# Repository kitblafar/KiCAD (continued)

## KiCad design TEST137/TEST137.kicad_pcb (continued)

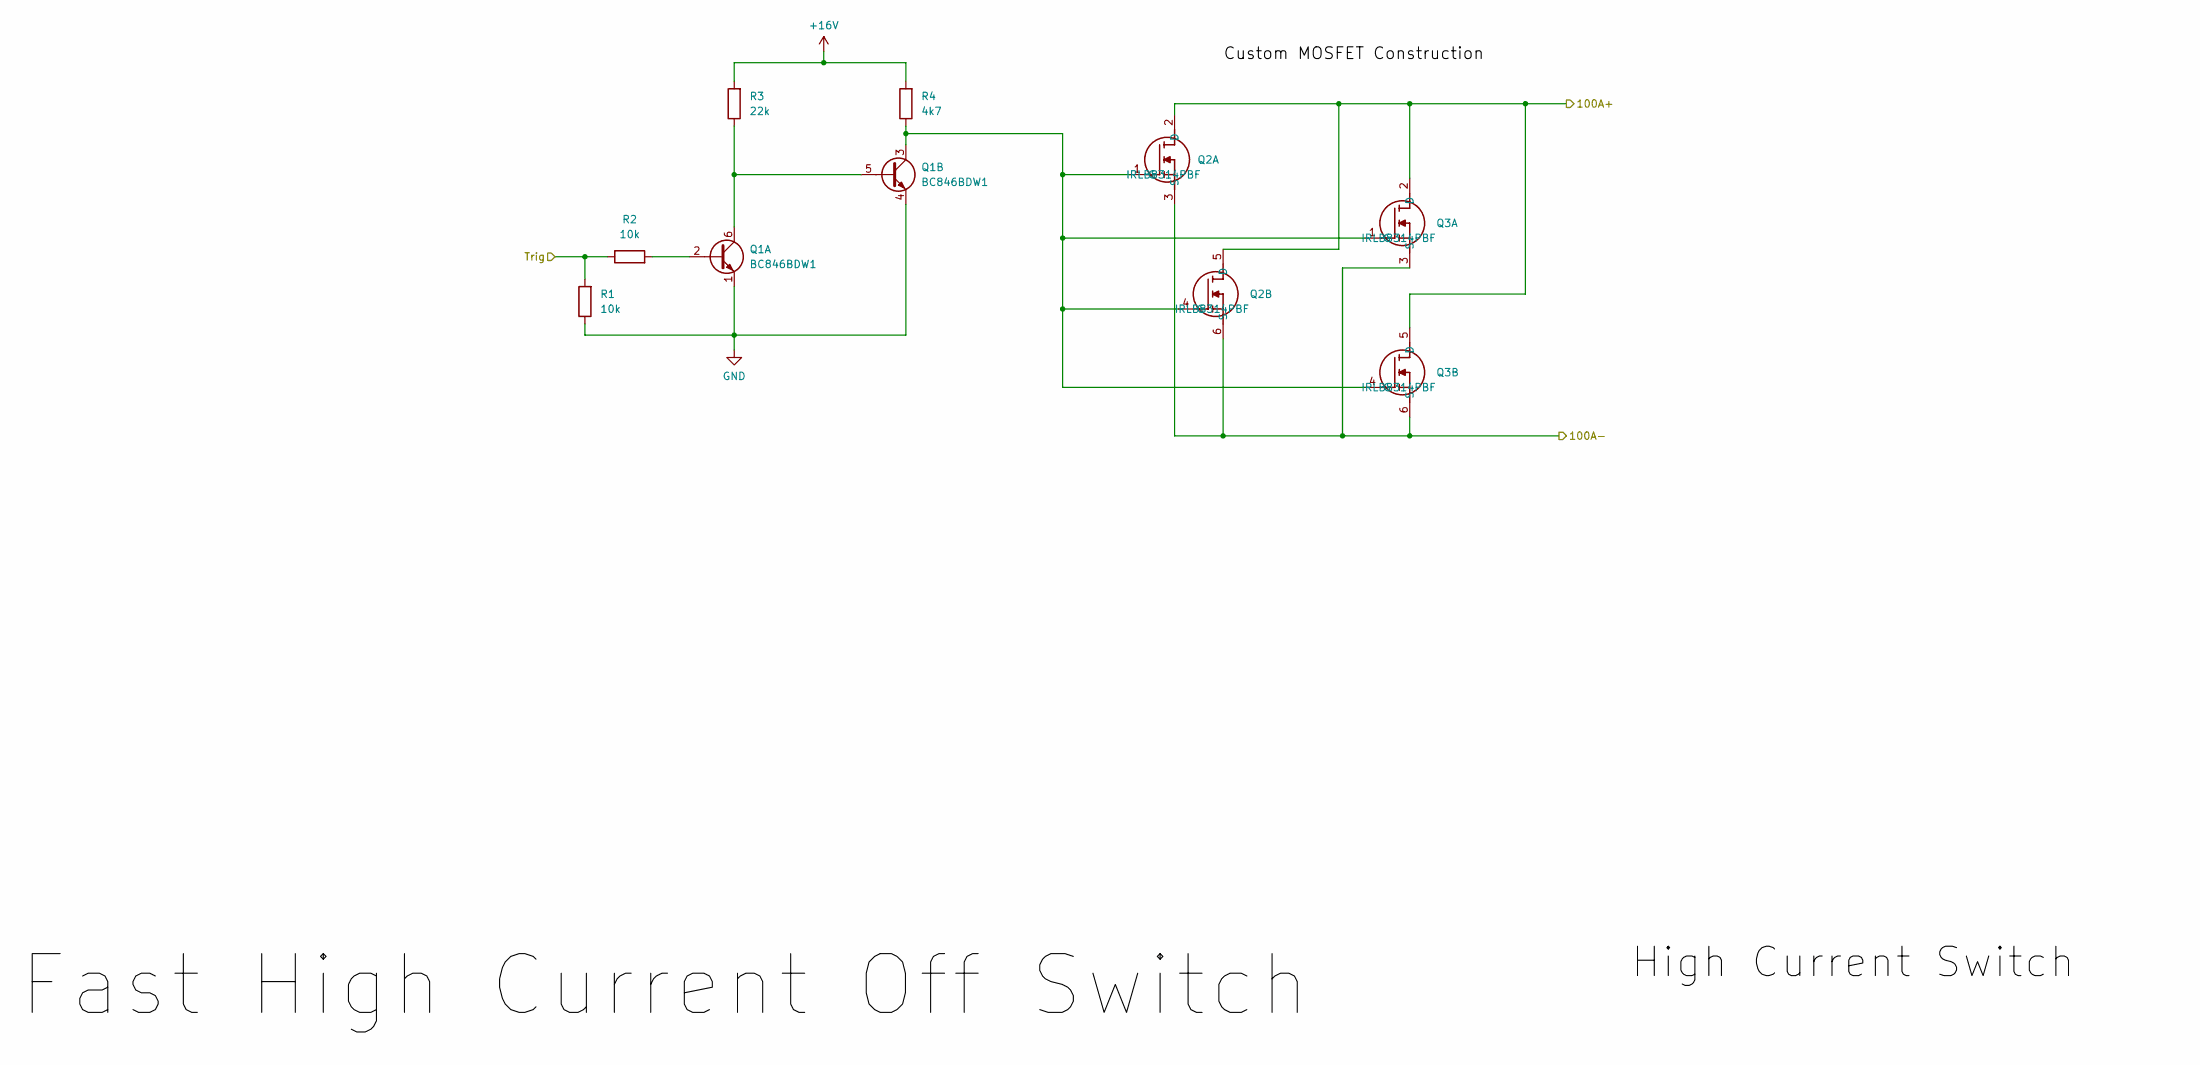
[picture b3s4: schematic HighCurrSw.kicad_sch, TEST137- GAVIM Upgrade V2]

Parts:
Q1: BC846BDW1; SOT-363_SC-70-6
Q2, Q3: IRLB8314PBF; MOSFETConstruct
R1, R2: 10k; R_0603_1608Metric_Pad0.98x0.95mm_HandSolder; Mouser Part Number LM321
R3: 22k; R_0603_1608Metric_Pad0.98x0.95mm_HandSolder
R4: 4k7; R_0603_1608Metric_Pad0.98x0.95mm_HandSolder

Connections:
+16V: R3.2, R4.2; also elsewhere on the board
/High Current Switch/100A+: Q2.2 (D), Q2.5 (D), Q3.2 (D), Q3.5 (D); also elsewhere on the board
/High Current Switch/100A-: Q2.3 (S), Q2.6 (S), Q3.3 (S), Q3.6 (S); also elsewhere on the board
/High Current Switch/Trig: R1.2, R2.1; also elsewhere on the board
GND: Q1.1 (E1), Q1.4 (E2), R1.1; also elsewhere on the board
unnamed: Q1.2 (B1), R2.2
unnamed: Q1.5 (B2), Q1.6 (C1), R3.1
unnamed: Q1.3 (C2), Q2.1 (G), Q2.4 (G), Q3.1 (G), Q3.4 (G), R4.1

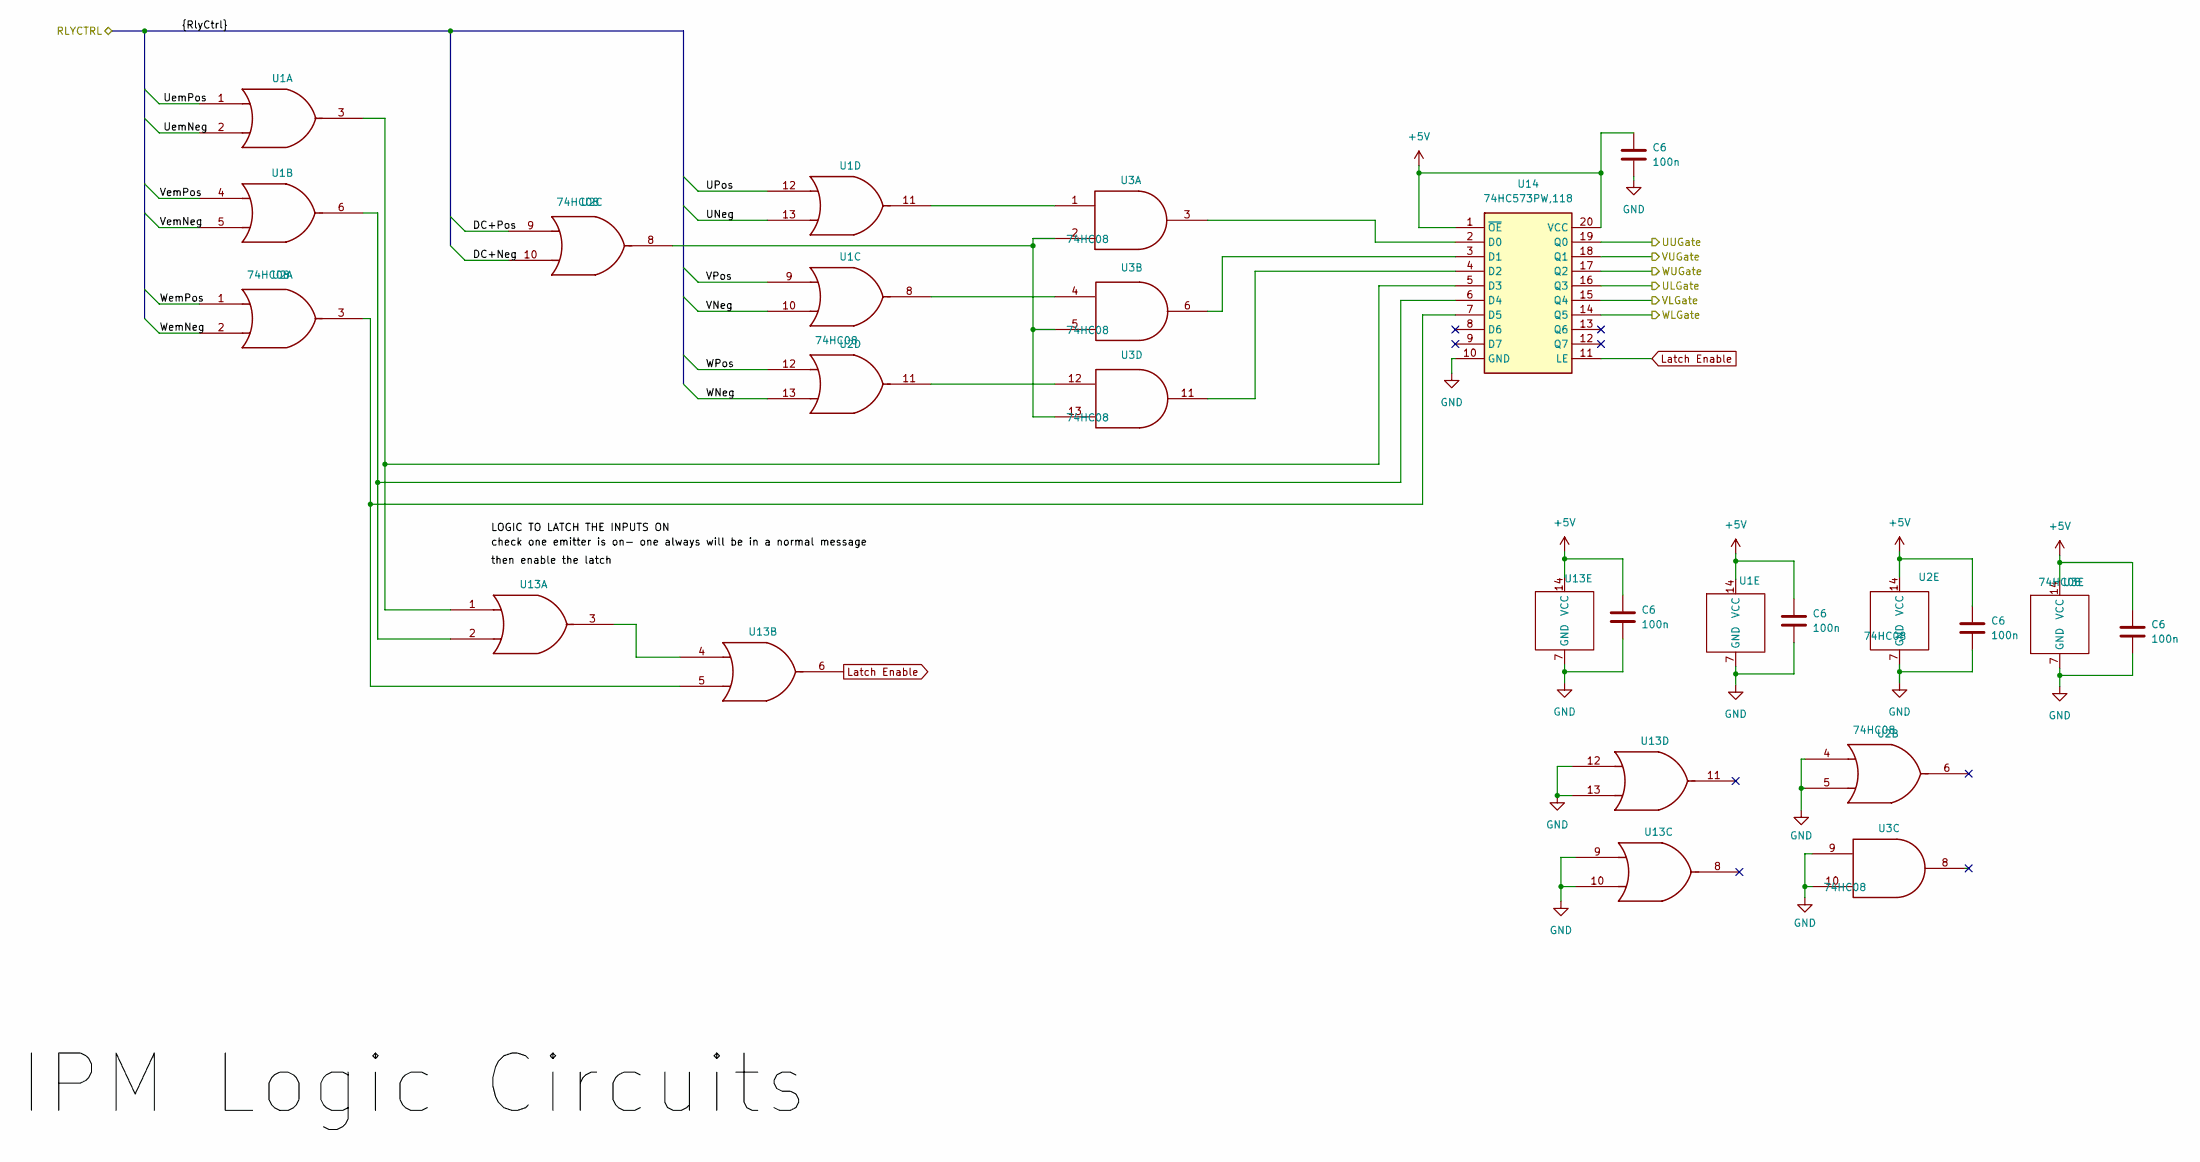
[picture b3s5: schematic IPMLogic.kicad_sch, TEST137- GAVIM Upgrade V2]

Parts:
C6: 100n; C_0603_1608Metric_Pad1.08x0.95mm_HandSolder
U1, U13: 74HC32; SO-14_3.9x8.65mm_P1.27mm
U2, U3: 74HC08; SO-14_3.9x8.65mm_P1.27mm
U14: 74HC573PW,118; SOP65P640X110-20N; Mouser Part Number 771-74HC573PW-T

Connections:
/DC+Neg: U2.10; also elsewhere on the board
/DC+Pos: U2.9; also elsewhere on the board
/IPM Logic/ULGate: U14.16 (Q3); also elsewhere on the board
/IPM Logic/UUGate: U14.19 (Q0); also elsewhere on the board
/IPM Logic/VLGate: U14.15 (Q4); also elsewhere on the board
/IPM Logic/VUGate: U14.18 (Q1); also elsewhere on the board
/IPM Logic/WLGate: U14.14 (Q5); also elsewhere on the board
/IPM Logic/WUGate: U14.17 (Q2); also elsewhere on the board
/UNeg: U1.13; also elsewhere on the board
/UPos: U1.12; also elsewhere on the board
/UemNeg: U1.2; also elsewhere on the board
/UemPos: U1.1; also elsewhere on the board
/VNeg: U1.10; also elsewhere on the board
/VPos: U1.9; also elsewhere on the board
/VemNeg: U1.5; also elsewhere on the board
/VemPos: U1.4; also elsewhere on the board
/WNeg: U2.13; also elsewhere on the board
/WPos: U2.12; also elsewhere on the board
/WemNeg: U2.2; also elsewhere on the board
/WemPos: U2.1; also elsewhere on the board
GND: C6.2, U1.7 (GND), U2.4, U2.5, U2.7 (GND), U3.7 (GND), U3.9, U3.10, U13.7 (GND), U13.9, U13.10, U13.12, U13.13, U14.10 (GND); also elsewhere on the board
Latch Enable: U13.6, U14.11 (LE)
unnamed: U1.8, U3.4
unnamed: U1.11, U3.1
unnamed: U2.8, U3.2, U3.5, U3.13
unnamed: U2.11, U3.12
unnamed: U13.3, U13.4
unnamed: U3.3, U14.2 (D0)
unnamed: U3.6, U14.3 (D1)
unnamed: U3.11, U14.4 (D2)
unnamed: U1.3, U13.1, U14.5 (D3)
unnamed: U1.6, U13.2, U14.6 (D4)
unnamed: U2.3, U13.5, U14.7 (D5)

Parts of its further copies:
C9, C12, C15, C18, C21, C24, C27, C28, C29, C30, C31: 100n; C_0603_1608Metric_Pad1.08x0.95mm_HandSolder

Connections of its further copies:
GND: C9.2, C12.2, C15.2, C18.2, C21.2, C24.2, C27.2, C28.2, C29.2, C30.2, C31.2; also elsewhere on the board

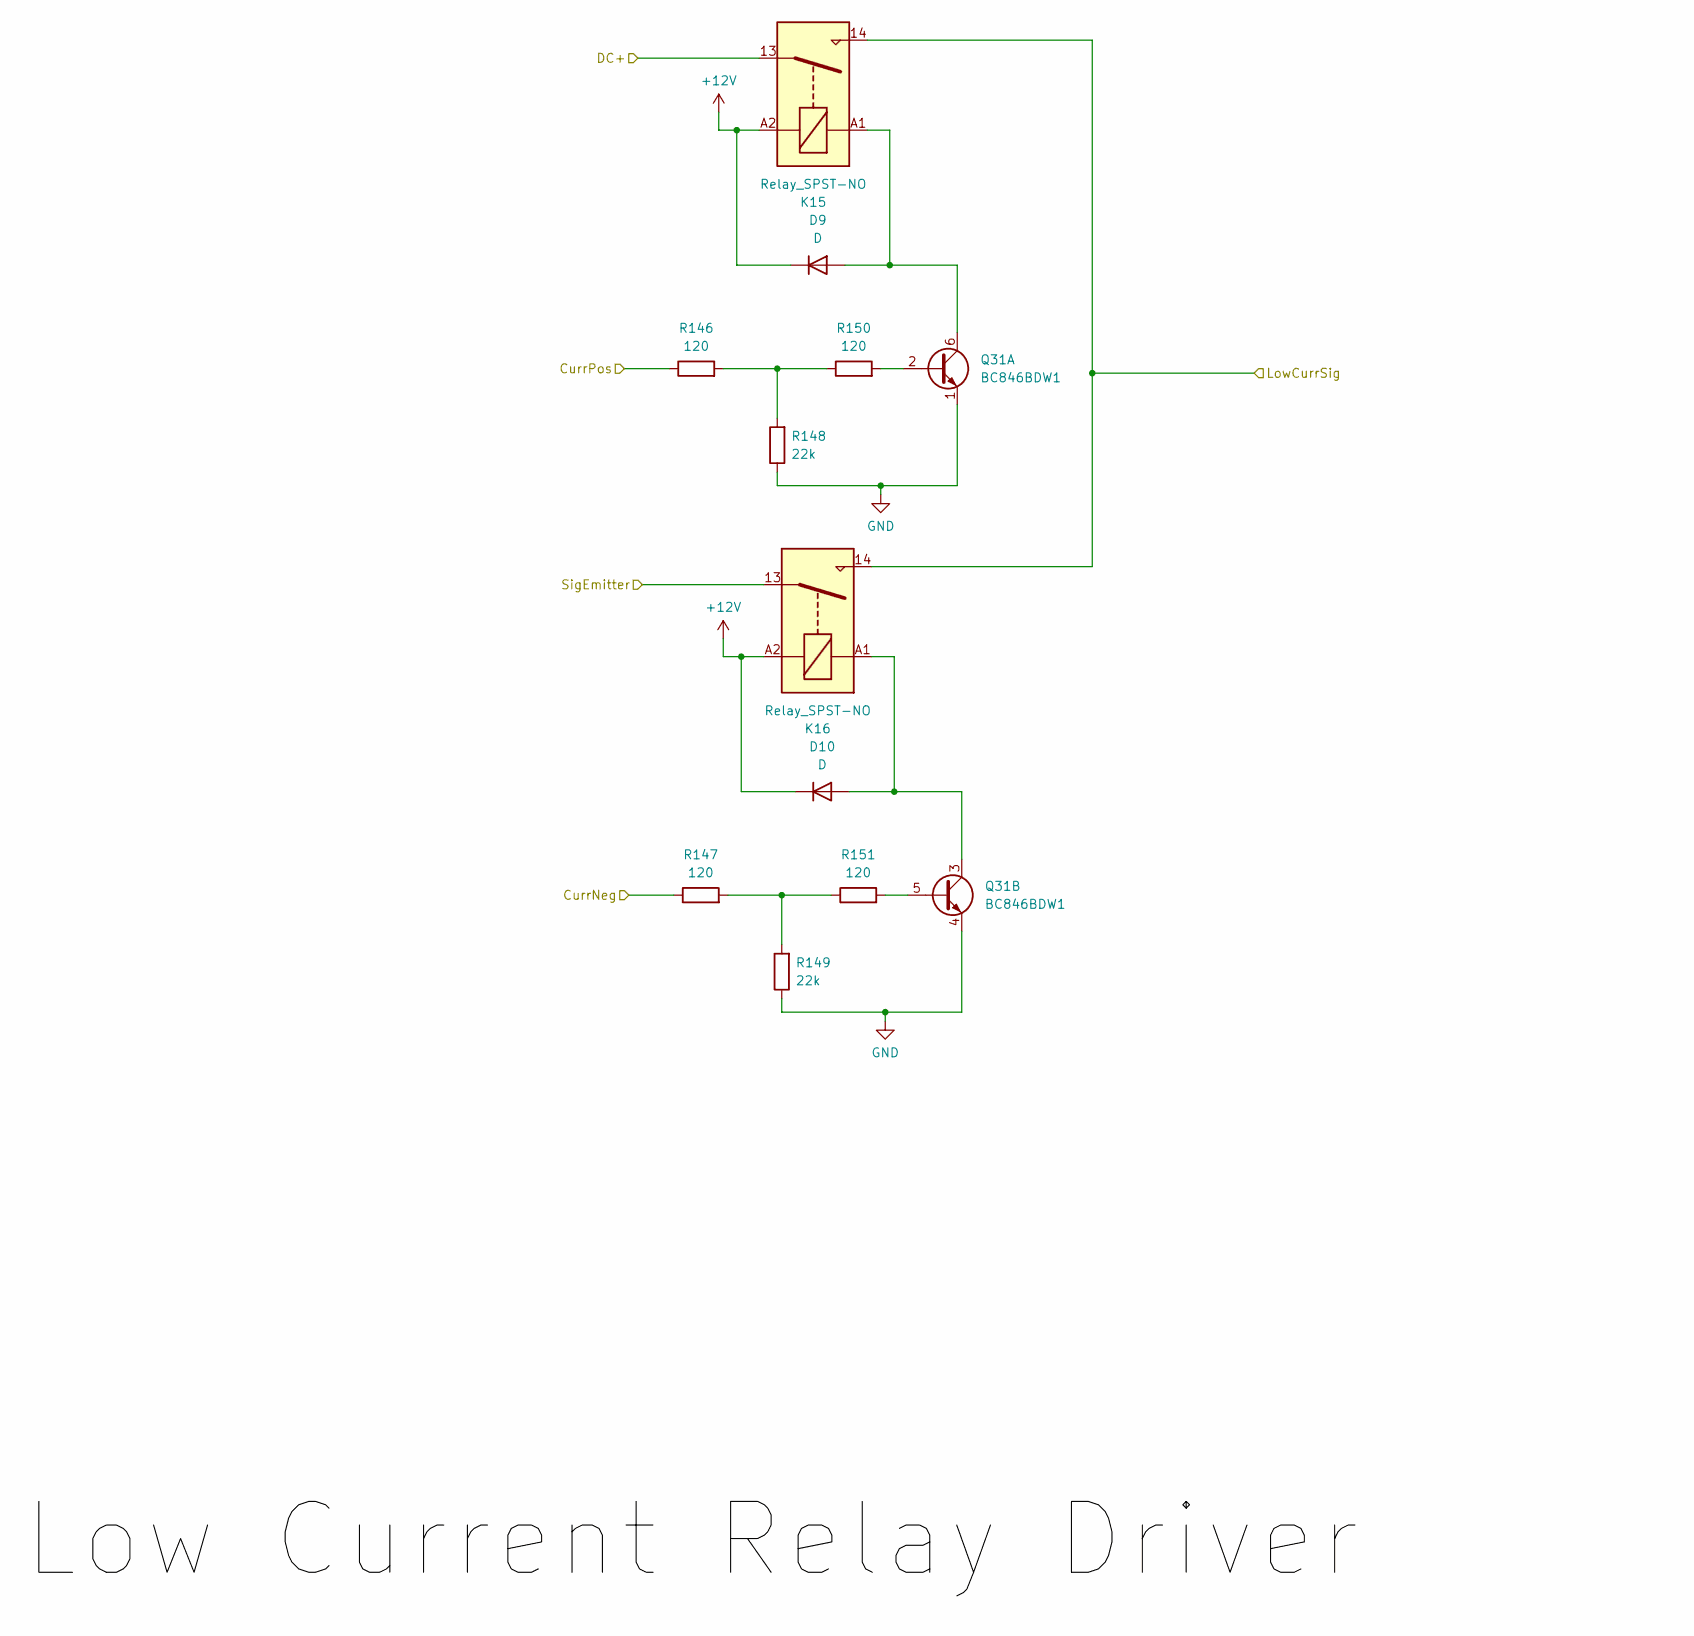
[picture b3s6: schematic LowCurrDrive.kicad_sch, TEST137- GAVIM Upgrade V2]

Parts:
D9, D10: D; D_DO-41_SOD81_P12.70mm_Horizontal
K15, K16: Relay_SPST-NO; HF32FAG012HSL1
Q31: BC846BDW1; SOT-363_SC-70-6
R146, R147, R150, R151: 120; R_0603_1608Metric_Pad0.98x0.95mm_HandSolder
R148, R149: 22k; R_0603_1608Metric_Pad0.98x0.95mm_HandSolder

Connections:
+12V: D9.1 (K), D10.1 (K), K15.A2, K16.A2; also elsewhere on the board
/CurrNeg: R147.1; also elsewhere on the board
/CurrPos: R146.1; also elsewhere on the board
/Low Current/DC+: K15.13; also elsewhere on the board
/Low Current/U Low Current Driver Sig/LowCurrSig: K15.14, K16.14; also elsewhere on the board
/Low Current/Uemitter: K16.13; also elsewhere on the board
GND: Q31.1 (E1), Q31.4 (E2), R148.1, R149.1; also elsewhere on the board
unnamed: D9.2 (A), K15.A1, Q31.6 (C1)
unnamed: D10.2 (A), K16.A1, Q31.3 (C2)
unnamed: Q31.2 (B1), R150.2
unnamed: Q31.5 (B2), R151.2
unnamed: R146.2, R148.2, R150.1
unnamed: R147.2, R149.2, R151.1

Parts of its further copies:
D12, D13, D14, D15, D16, D17, D18, D19, D20: D; D_DO-41_SOD81_P12.70mm_Horizontal
K17, K18, K19, K20, K21, K22, K23, K24, K25, K26: Relay_SPST-NO; HF32FAG012HSL1
Q27, Q32, Q40, Q41, Q45: BC846BDW1; SOT-363_SC-70-6
R152, R153, R156, R157, R158, R159, R162, R163, R164, R165, R168, R169, R170, R171, R174, R175, R176, R177, R180, R181: 120; R_0603_1608Metric_Pad0.98x0.95mm_HandSolder
R154, R155, R160, R161, R166, R167, R172, R173, R178, R179: 22k; R_0603_1608Metric_Pad0.98x0.95mm_HandSolder

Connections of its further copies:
+12V: D12.1 (K), D13.1 (K), D14.1 (K), D15.1 (K), D16.1 (K), D17.1 (K), D18.1 (K), D19.1 (K), D20.1 (K), K17.A2, K18.A2, K19.A2, K20.A2, K21.A2, K22.A2, K23.A2, K24.A2, K25.A2, K26.A2; also elsewhere on the board
/CurrNeg: R153.1, R159.1, R165.1, R171.1, R177.1; also elsewhere on the board
/CurrPos: R152.1, R158.1, R164.1, R170.1, R176.1; also elsewhere on the board
/Low Current/DC+: K17.13, K19.13, K21.13, K23.13, K25.13; also elsewhere on the board
/Low Current/S1_GND: K17.14, K18.14; also elsewhere on the board
/Low Current/S2_GND: K21.14, K22.14; also elsewhere on the board
/Low Current/S3_GND: K25.14, K26.14; also elsewhere on the board
/Low Current/Uemitter: K18.13; also elsewhere on the board
/Low Current/V Low Current Driver Sig/LowCurrSig: K19.14, K20.14; also elsewhere on the board
/Low Current/Vemitter: K20.13, K22.13; also elsewhere on the board
/Low Current/W Low Current Driver Sig/LowCurrSig: K23.14, K24.14; also elsewhere on the board
/Low Current/Wemitter: K24.13, K26.13; also elsewhere on the board
GND: Q27.1 (E1), Q27.4 (E2), Q32.1 (E1), Q32.4 (E2), Q40.1 (E1), Q40.4 (E2), Q41.1 (E1), Q41.4 (E2), Q45.1 (E1), Q45.4 (E2), R154.1, R155.1, R160.1, R161.1, R166.1, R167.1, R172.1, R173.1, R178.1, R179.1; also elsewhere on the board
unnamed 61: K17.A1, Q32.6 (C1); also elsewhere on the board
unnamed: D12.2 (A), K18.A1, Q32.3 (C2)
unnamed: D13.2 (A), K19.A1, Q27.6 (C1)
unnamed: D14.2 (A), K20.A1, Q27.3 (C2)
unnamed: D15.2 (A), K21.A1, Q40.6 (C1)
unnamed: D16.2 (A), K22.A1, Q40.3 (C2)
unnamed: D17.2 (A), K23.A1, Q41.6 (C1)
unnamed: D18.2 (A), K24.A1, Q41.3 (C2)
unnamed: D19.2 (A), K25.A1, Q45.6 (C1)
unnamed: D20.2 (A), K26.A1, Q45.3 (C2)
unnamed: Q27.2 (B1), R162.2
unnamed: Q27.5 (B2), R163.2
unnamed: Q32.2 (B1), R156.2
unnamed: Q32.5 (B2), R157.2
unnamed: Q40.2 (B1), R168.2
unnamed: Q40.5 (B2), R169.2
unnamed: Q41.2 (B1), R174.2
unnamed: Q41.5 (B2), R175.2
unnamed: Q45.2 (B1), R180.2
unnamed: Q45.5 (B2), R181.2
unnamed: R152.2, R154.2, R156.1
unnamed: R153.2, R155.2, R157.1
unnamed: R158.2, R160.2, R162.1
unnamed: R159.2, R161.2, R163.1
unnamed: R164.2, R166.2, R168.1
unnamed: R165.2, R167.2, R169.1
unnamed: R170.2, R172.2, R174.1
unnamed: R171.2, R173.2, R175.1
unnamed: R176.2, R178.2, R180.1
unnamed: R177.2, R179.2, R181.1

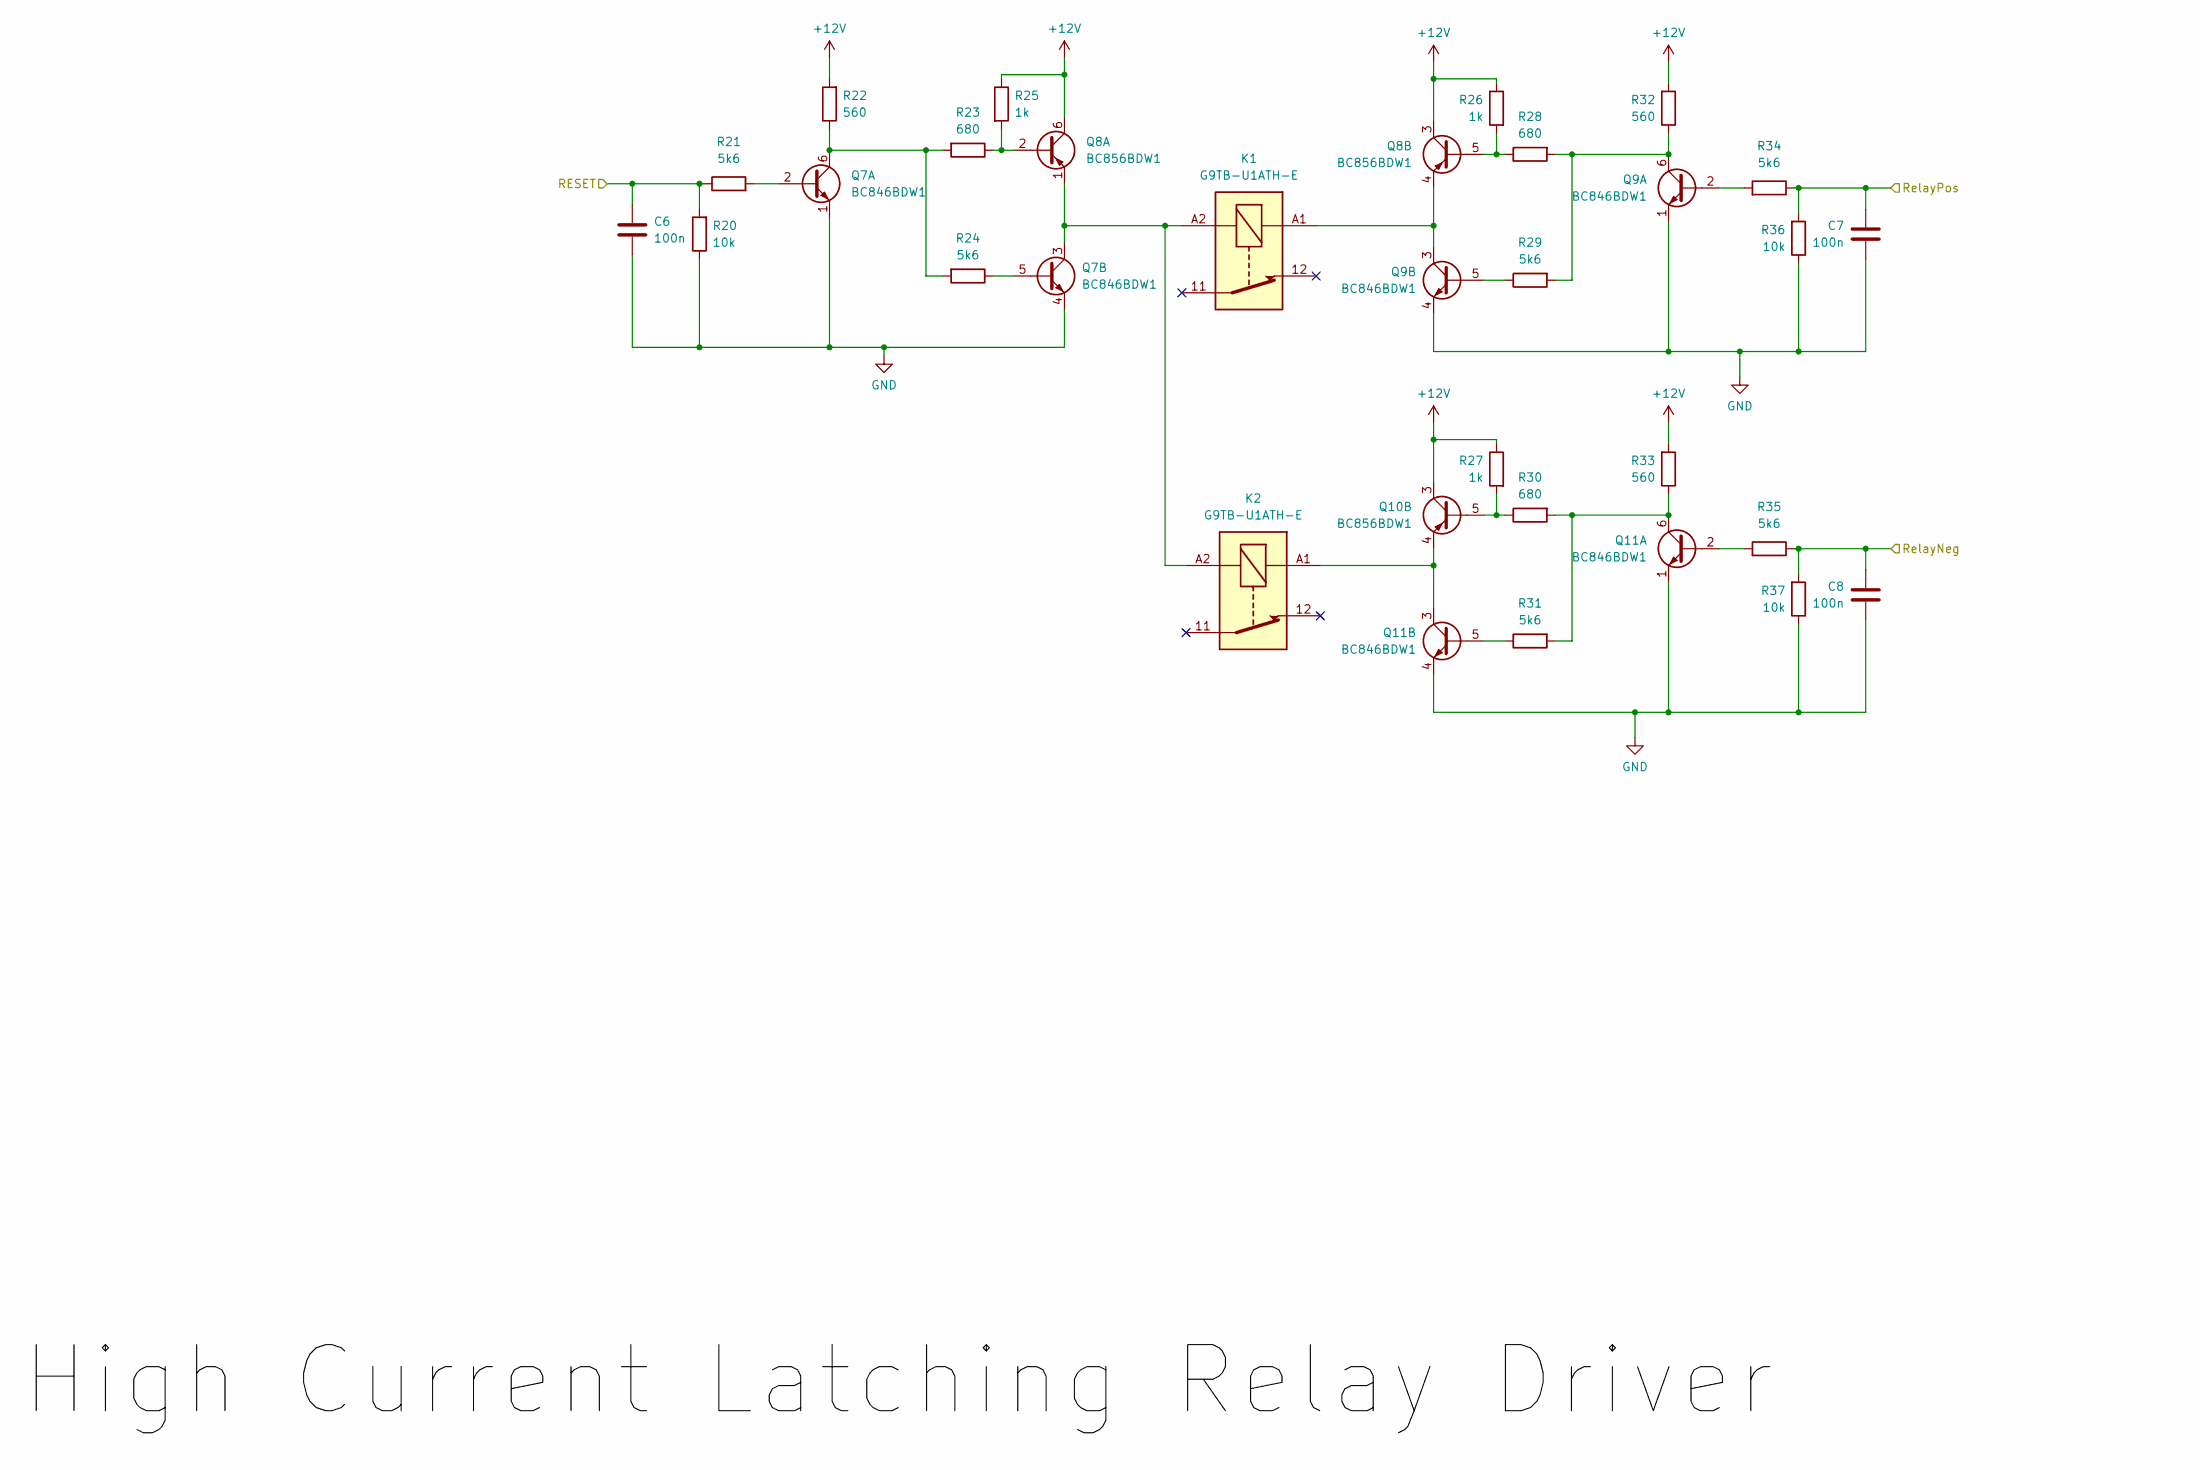
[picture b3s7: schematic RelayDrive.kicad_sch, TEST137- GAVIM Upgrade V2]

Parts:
C6, C7, C8: 100n; C_0603_1608Metric_Pad1.08x0.95mm_HandSolder
K1, K2: G9TB-U1ATH-E; G9TB
Q7, Q9, Q11: BC846BDW1; SOT-363_SC-70-6
Q8, Q10: BC856BDW1; SOT-363_SC-70-6
R20, R36, R37: 10k; R_0603_1608Metric_Pad0.98x0.95mm_HandSolder; Mouser Part Number LM321
R21, R24, R29, R31, R34, R35: 5k6; R_0603_1608Metric_Pad0.98x0.95mm_HandSolder
R22, R32, R33: 560; R_1206_3216Metric_Pad1.30x1.75mm_HandSolder
R23, R28, R30: 680; R_0603_1608Metric_Pad0.98x0.95mm_HandSolder
R25, R26, R27: 1k; R_0603_1608Metric_Pad0.98x0.95mm_HandSolder

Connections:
+12V: Q8.3 (C2), Q8.6 (C1), Q10.3 (C2), R22.2, R25.1, R26.1, R27.1, R32.2, R33.2; also elsewhere on the board
/DC+Neg: C8.1, R35.1, R37.2; also elsewhere on the board
/DC+Pos: C7.1, R34.1, R36.2; also elsewhere on the board
GND: C6.2, C7.2, C8.2, Q7.1 (E1), Q7.4 (E2), Q9.1 (E1), Q9.4 (E2), Q11.1 (E1), Q11.4 (E2), R20.1, R36.1, R37.1; also elsewhere on the board
unnamed: Q7.2 (B1), R21.2
unnamed: Q7.6 (C1), R22.1, R23.2, R24.2
unnamed: Q7.5 (B2), R24.1
unnamed: K1.A2, K2.A2, Q7.3 (C2), Q8.1 (E1)
unnamed: Q8.2 (B1), R23.1, R25.2
unnamed: Q8.5 (B2), R26.2, R28.1
unnamed: K1.A1, Q8.4 (E2), Q9.3 (C2)
unnamed: Q9.2 (B1), R34.2
unnamed: Q9.6 (C1), R28.2, R29.2, R32.1
unnamed: Q9.5 (B2), R29.1
unnamed: Q10.5 (B2), R27.2, R30.1
unnamed: K2.A1, Q10.4 (E2), Q11.3 (C2)
unnamed: Q11.2 (B1), R35.2
unnamed: Q11.6 (C1), R30.2, R31.2, R33.1
unnamed: Q11.5 (B2), R31.1

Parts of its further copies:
C9, C10, C11, C12, C13, C14, C15, C16, C17, C18, C19, C20, C21, C22, C23, C24, C25, C26: 100n; C_0603_1608Metric_Pad1.08x0.95mm_HandSolder
K3, K4, K5, K6, K7, K8, K9, K10, K11, K12, K13, K14: G9TB-U1ATH-E; G9TB
Q4, Q12, Q14, Q16, Q17, Q19, Q21, Q22, Q24, Q26, Q29, Q33, Q34, Q35, Q38, Q39, Q42, Q44: BC846BDW1; SOT-363_SC-70-6
Q5, Q13, Q15, Q18, Q20, Q23, Q25, Q28, Q30, Q36, Q37, Q43: BC856BDW1; SOT-363_SC-70-6
R38, R54, R55, R56, R72, R73, R74, R90, R91, R92, R108, R109, R110, R126, R127, R128, R144, R145: 10k; R_0603_1608Metric_Pad0.98x0.95mm_HandSolder; Mouser Part Number LM321
R39, R42, R47, R49, R52, R53, R57, R60, R65, R67, R70, R71, R75, R78, R83, R85, R88, R89, R93, R96, R101, R103, R106, R107, R111, R114, R119, R121, R124, R125, R129, R132, R137, R139, R142, R143: 5k6; R_0603_1608Metric_Pad0.98x0.95mm_HandSolder
R40, R50, R51, R58, R68, R69, R76, R86, R87, R94, R104, R105, R112, R122, R123, R130, R140, R141: 560; R_1206_3216Metric_Pad1.30x1.75mm_HandSolder
R41, R46, R48, R59, R64, R66, R77, R82, R84, R95, R100, R102, R113, R118, R120, R131, R136, R138: 680; R_0603_1608Metric_Pad0.98x0.95mm_HandSolder
R43, R44, R45, R61, R62, R63, R79, R80, R81, R97, R98, R99, R115, R116, R117, R133, R134, R135: 1k; R_0603_1608Metric_Pad0.98x0.95mm_HandSolder

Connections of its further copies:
+12V: Q5.3 (C2), Q13.3 (C2), Q13.6 (C1), Q15.3 (C2), Q18.3 (C2), Q18.6 (C1), Q20.3 (C2), Q23.3 (C2), Q23.6 (C1), Q25.3 (C2), Q28.3 (C2), Q28.6 (C1), Q30.3 (C2), Q30.6 (C1), Q36.3 (C2), Q36.6 (C1), Q37.3 (C2), Q43.3 (C2), R40.2, R43.1, R44.1, R45.1, R50.2, R51.2, R58.2, R61.1, R62.1, R63.1, R68.2, R69.2, R76.2, R79.1, R80.1, R81.1, R86.2, R87.2, R94.2, R97.1, R98.1, R99.1, R104.2, R105.2, R112.2, R115.1, R116.1, R117.1, R122.2, R123.2, R130.2, R133.1, R134.1, R135.1, R140.2, R141.2; also elsewhere on the board
/UNeg: C11.1, R53.1, R55.2; also elsewhere on the board
/UPos: C10.1, R52.1, R54.2; also elsewhere on the board
/UemNeg: C20.1, R107.1, R109.2; also elsewhere on the board
/UemPos: C19.1, R106.1, R108.2; also elsewhere on the board
/VNeg: C14.1, R71.1, R73.2; also elsewhere on the board
/VPos: C13.1, R70.1, R72.2; also elsewhere on the board
/VemNeg: C23.1, R125.1, R127.2; also elsewhere on the board
/VemPos: C22.1, R124.1, R126.2; also elsewhere on the board
/WNeg: C17.1, R89.1, R91.2; also elsewhere on the board
/WPos: C16.1, R88.1, R90.2; also elsewhere on the board
/WemNeg: C26.1, R143.1, R145.2; also elsewhere on the board
/WemPos: C25.1, R142.1, R144.2; also elsewhere on the board
GND: C9.2, C10.2, C11.2, C12.2, C13.2, C14.2, C15.2, C16.2, C17.2, C18.2, C19.2, C20.2, C21.2, C22.2, C23.2, C24.2, C25.2, C26.2, Q4.1 (E1), Q4.4 (E2), Q12.1 (E1), Q12.4 (E2), Q14.1 (E1), Q14.4 (E2), Q16.1 (E1), Q16.4 (E2), Q17.1 (E1), Q17.4 (E2), Q19.1 (E1), Q19.4 (E2), Q21.1 (E1), Q21.4 (E2), Q22.1 (E1), Q22.4 (E2), Q24.1 (E1), Q24.4 (E2), Q26.1 (E1), Q26.4 (E2), Q29.1 (E1), Q29.4 (E2), Q33.1 (E1), Q33.4 (E2), Q34.1 (E1), Q34.4 (E2), Q35.1 (E1), Q35.4 (E2), Q38.1 (E1), Q38.4 (E2), Q39.1 (E1), Q39.4 (E2), Q42.1 (E1), Q42.4 (E2), Q44.1 (E1), Q44.4 (E2), R38.1, R54.1, R55.1, R56.1, R72.1, R73.1, R74.1, R90.1, R91.1, R92.1, R108.1, R109.1, R110.1, R126.1, R127.1, R128.1, R144.1, R145.1; also elsewhere on the board
unnamed: Q4.2 (B1), R111.2
unnamed: Q4.6 (C1), R112.1, R113.2, R114.2
unnamed: Q4.5 (B2), R114.1
unnamed: Q5.5 (B2), R99.2, R102.1
unnamed: Q12.2 (B1), R39.2
unnamed: Q12.6 (C1), R40.1, R41.2, R42.2
unnamed: Q12.5 (B2), R42.1
unnamed: K3.A2, K4.A2, Q12.3 (C2), Q13.1 (E1)
unnamed: Q13.2 (B1), R41.1, R43.2
unnamed: Q13.5 (B2), R44.2, R46.1
unnamed: K3.A1, Q13.4 (E2), Q14.3 (C2)
unnamed: Q14.2 (B1), R52.2
unnamed: Q14.6 (C1), R46.2, R47.2, R50.1
unnamed: Q14.5 (B2), R47.1
unnamed: Q15.5 (B2), R45.2, R48.1
unnamed: K4.A1, Q15.4 (E2), Q16.3 (C2)
unnamed: Q16.2 (B1), R53.2
unnamed: Q16.6 (C1), R48.2, R49.2, R51.1
unnamed: Q16.5 (B2), R49.1
unnamed: Q17.2 (B1), R57.2
unnamed: Q17.6 (C1), R58.1, R59.2, R60.2
unnamed: Q17.5 (B2), R60.1
unnamed: K5.A2, K6.A2, Q17.3 (C2), Q18.1 (E1)
unnamed: Q18.2 (B1), R59.1, R61.2
unnamed: Q18.5 (B2), R62.2, R64.1
unnamed: K5.A1, Q18.4 (E2), Q19.3 (C2)
unnamed: Q19.2 (B1), R70.2
unnamed: Q19.6 (C1), R64.2, R65.2, R68.1
unnamed: Q19.5 (B2), R65.1
unnamed: Q20.5 (B2), R63.2, R66.1
unnamed: K6.A1, Q20.4 (E2), Q21.3 (C2)
unnamed: Q21.2 (B1), R71.2
unnamed: Q21.6 (C1), R66.2, R67.2, R69.1
unnamed: Q21.5 (B2), R67.1
unnamed: Q22.2 (B1), R75.2
unnamed: Q22.6 (C1), R76.1, R77.2, R78.2
unnamed: Q22.5 (B2), R78.1
unnamed: K7.A2, K8.A2, Q22.3 (C2), Q23.1 (E1)
unnamed: Q23.2 (B1), R77.1, R79.2
unnamed: Q23.5 (B2), R80.2, R82.1
unnamed: K7.A1, Q23.4 (E2), Q24.3 (C2)
unnamed: Q24.2 (B1), R88.2
unnamed: Q24.6 (C1), R82.2, R83.2, R86.1
unnamed: Q24.5 (B2), R83.1
unnamed: Q25.5 (B2), R81.2, R84.1
unnamed: K8.A1, Q25.4 (E2), Q26.3 (C2)
unnamed: Q26.2 (B1), R89.2
unnamed: Q26.6 (C1), R84.2, R85.2, R87.1
unnamed: Q26.5 (B2), R85.1
unnamed: Q28.2 (B1), R95.1, R97.2
unnamed: K9.A2, K10.A2, Q28.1 (E1), Q29.3 (C2)
unnamed: Q28.5 (B2), R98.2, R100.1
unnamed: K9.A1, Q28.4 (E2), Q33.3 (C2)
unnamed: Q29.2 (B1), R93.2
unnamed: Q29.6 (C1), R94.1, R95.2, R96.2
unnamed: Q29.5 (B2), R96.1
unnamed: Q30.2 (B1), R113.1, R115.2
unnamed: K11.A2, K12.A2, Q4.3 (C2), Q30.1 (E1)
unnamed: Q30.5 (B2), R116.2, R118.1
unnamed: K11.A1, Q30.4 (E2), Q38.3 (C2)
unnamed: Q33.2 (B1), R106.2
unnamed: Q33.6 (C1), R100.2, R101.2, R104.1
unnamed: Q33.5 (B2), R101.1
unnamed: Q34.2 (B1), R107.2
unnamed: Q34.6 (C1), R102.2, R103.2, R105.1
unnamed: Q34.5 (B2), R103.1
unnamed: K10.A1, Q5.4 (E2), Q34.3 (C2)
unnamed: Q35.2 (B1), R129.2
unnamed: Q35.6 (C1), R130.1, R131.2, R132.2
unnamed: Q35.5 (B2), R132.1
unnamed: K13.A2, K14.A2, Q35.3 (C2), Q36.1 (E1)
unnamed: Q36.2 (B1), R131.1, R133.2
unnamed: Q36.5 (B2), R134.2, R136.1
unnamed: K13.A1, Q36.4 (E2), Q42.3 (C2)
unnamed: Q37.5 (B2), R117.2, R120.1
unnamed: K12.A1, Q37.4 (E2), Q39.3 (C2)
unnamed: Q38.2 (B1), R124.2
unnamed: Q38.6 (C1), R118.2, R119.2, R122.1
unnamed: Q38.5 (B2), R119.1
unnamed: Q39.2 (B1), R125.2
unnamed: Q39.6 (C1), R120.2, R121.2, R123.1
unnamed: Q39.5 (B2), R121.1
unnamed: Q42.2 (B1), R142.2
unnamed: Q42.6 (C1), R136.2, R137.2, R140.1
unnamed: Q42.5 (B2), R137.1
unnamed: Q43.5 (B2), R135.2, R138.1
unnamed: K14.A1, Q43.4 (E2), Q44.3 (C2)
unnamed: Q44.2 (B1), R143.2
unnamed: Q44.6 (C1), R138.2, R139.2, R141.1
unnamed: Q44.5 (B2), R139.1

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
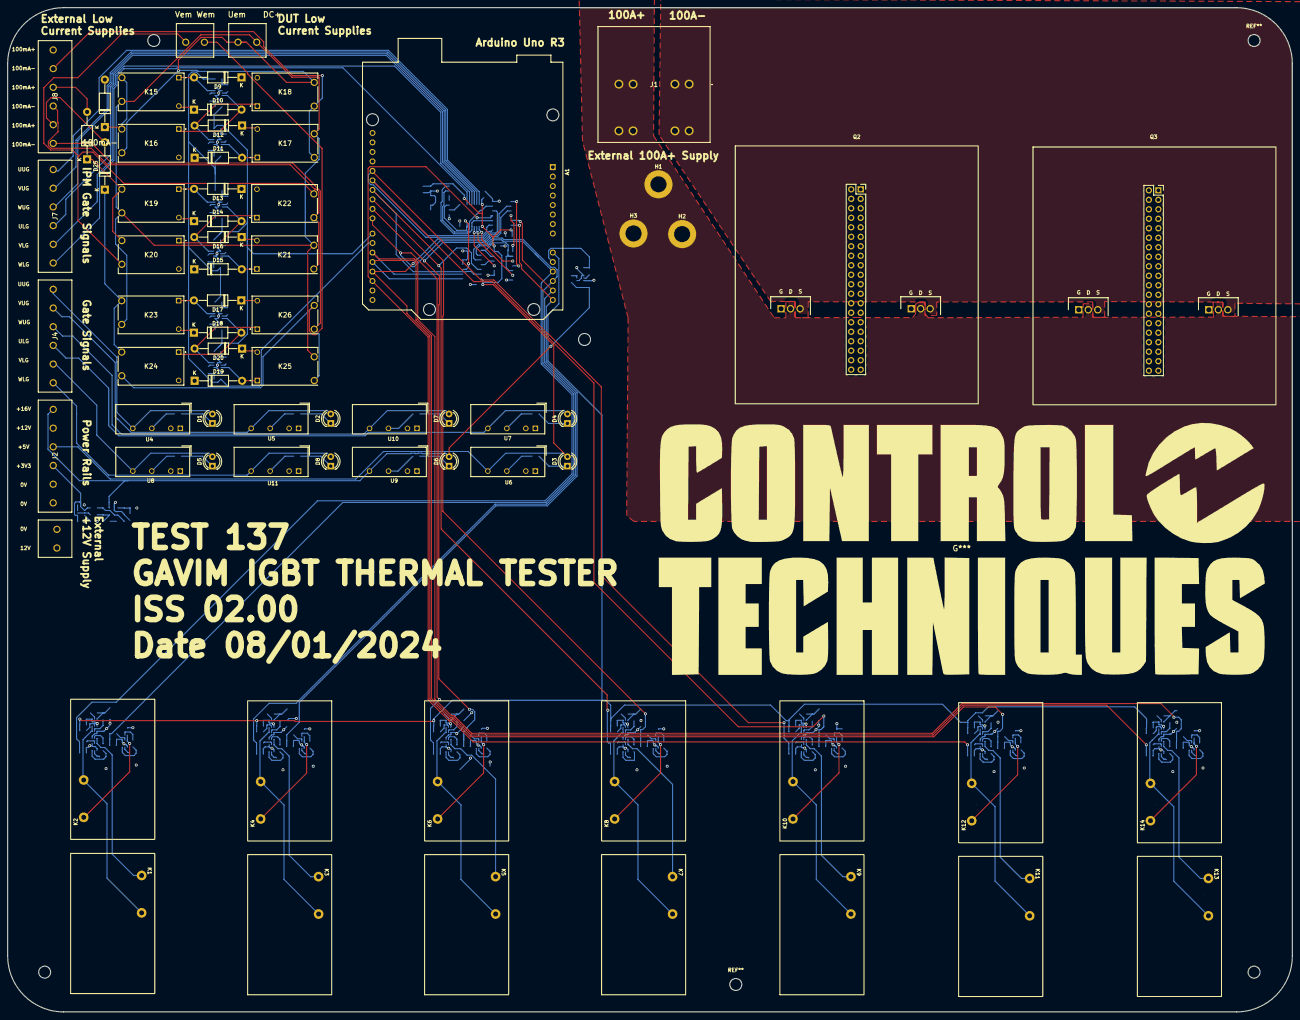
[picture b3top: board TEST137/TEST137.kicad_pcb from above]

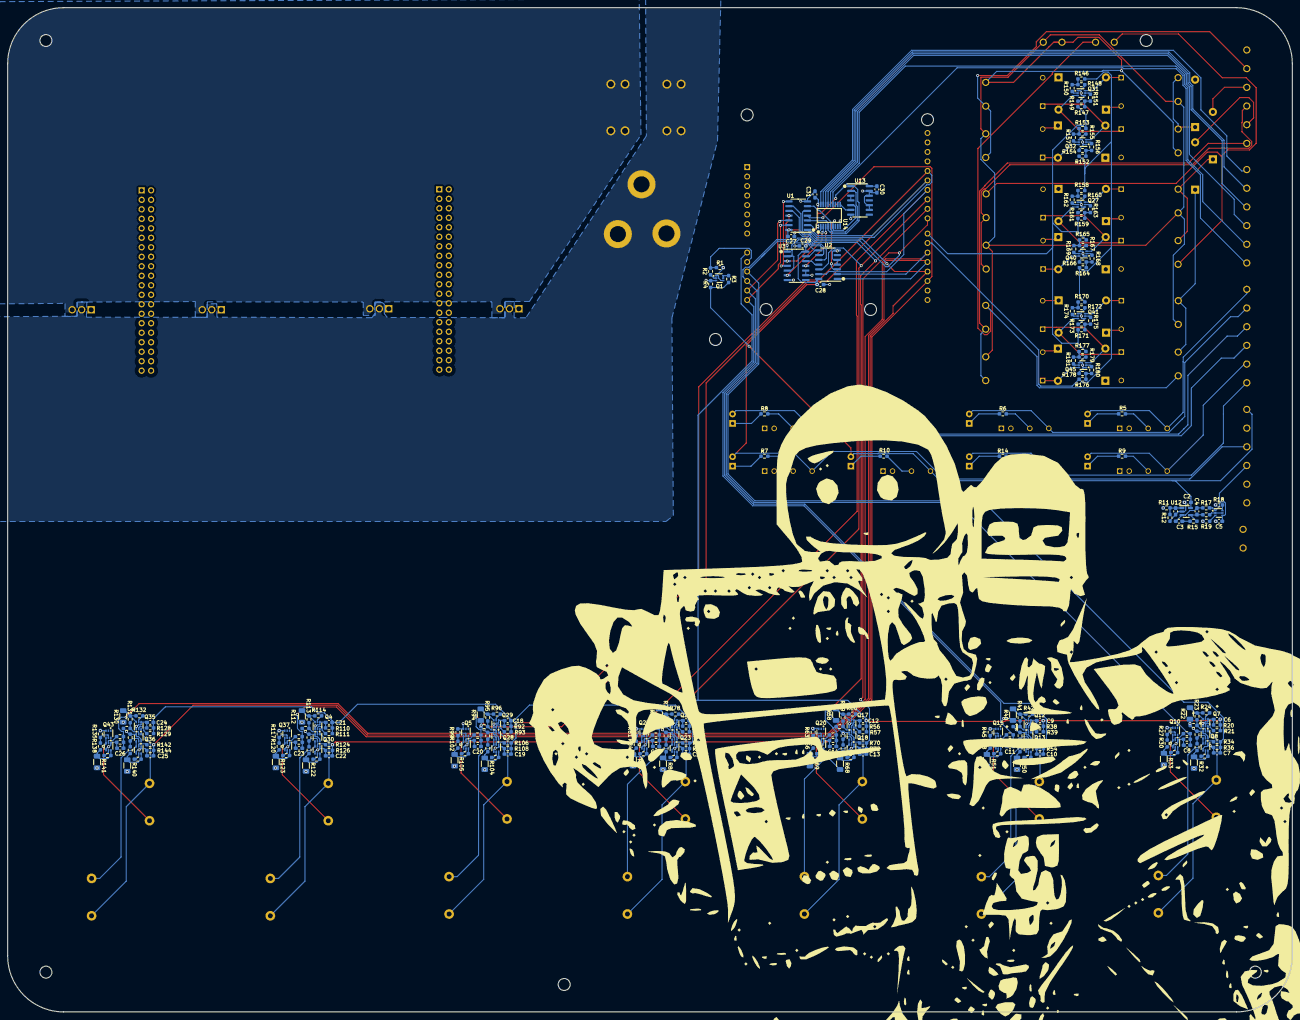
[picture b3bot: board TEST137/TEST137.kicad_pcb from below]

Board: 4 copper layers, 343.8 x 268.7 mm, 332 parts (261 on the bottom side), 229 nets.
